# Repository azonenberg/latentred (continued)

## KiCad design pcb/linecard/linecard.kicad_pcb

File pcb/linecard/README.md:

# 24-port non-PoE 10/100/1000baseT QSGMII line card

Input: 12V at 1.25A max, fused at 3A to be conservative.

Expect ~15W max power consumption, less under typical operation

## ERRATA

v0.1: right LED on the RJ45 is swapped between upper and lower ports

## Power

### Needs

* VDD (1.0V): 1.15A per PHY, 2.3A total
* VDD_A (1.0V): 180 mA per PHY, 360 mA total
* VDD_AH (2.5V): 1.37A per PHY, 2.74A total
* VDD_AL (1.0V): 190 mA per PHY, 380 total
* VDD_IO (2.5V): 60 mA per PHY, 120 mA total
* VDD_VS (1.0V): 90 mA per PHY, 180 mA total
* Plus a 3.3V standby rail for the management MCU

## I2C address map

* 0x80: INA230 on 3V3
* 0x82: INA230 on 2V5
* 0x84: INA230 on 1V0
* 0x86: INA230 on 1V0_2
* 0x90: AT30TS74 near PHY 0
* 0x92: AT30ST74 near PHY 1
* 0x94: AT30TS74 near power supply

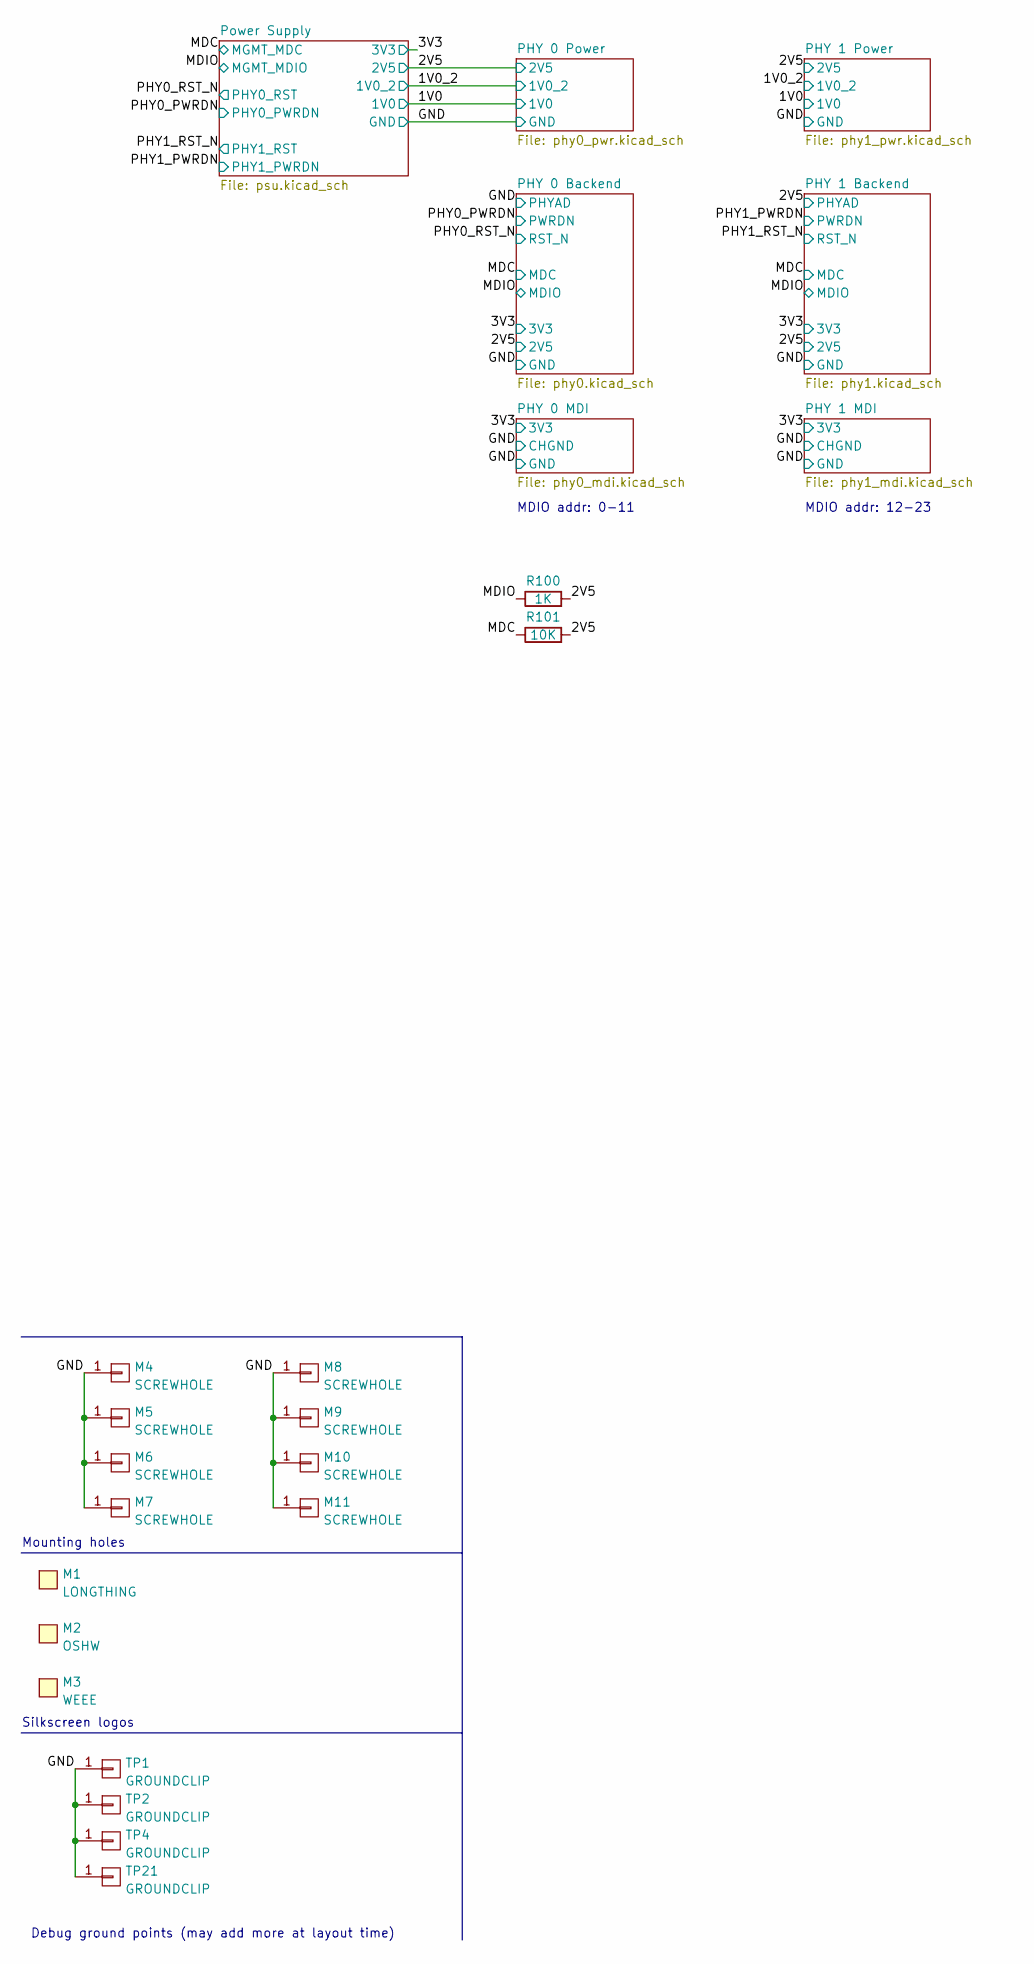
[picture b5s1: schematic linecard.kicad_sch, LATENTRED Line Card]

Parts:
M1: LONGTHING; LONGTHING-600DPI
M2: OSHW; Logo_silk_OSHW_6x6mm
M3: WEEE; Logo_silk_WEEE_3.4x5mm
M4, M5, M6, M7, M8, M9, M10, M11: SCREWHOLE; MECHANICAL_CLEARANCEHOLE_4_40
R100: 1K; EIA_0402_RES_NOSILK
R101: 10K; EIA_0402_RES_NOSILK
TP1, TP2, TP4, TP21: GROUNDCLIP; TESTPOINT_SMT_KEYSTONE_5016

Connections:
/2V5: R100.2, R101.2; also elsewhere on the board
/MDC: R101.1; also elsewhere on the board
/MDIO: R100.1; also elsewhere on the board

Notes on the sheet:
Silkscreen logos
Debug ground points (may add more at layout time)
MDIO addr: 0-11
Mounting holes
MDIO addr: 12-23

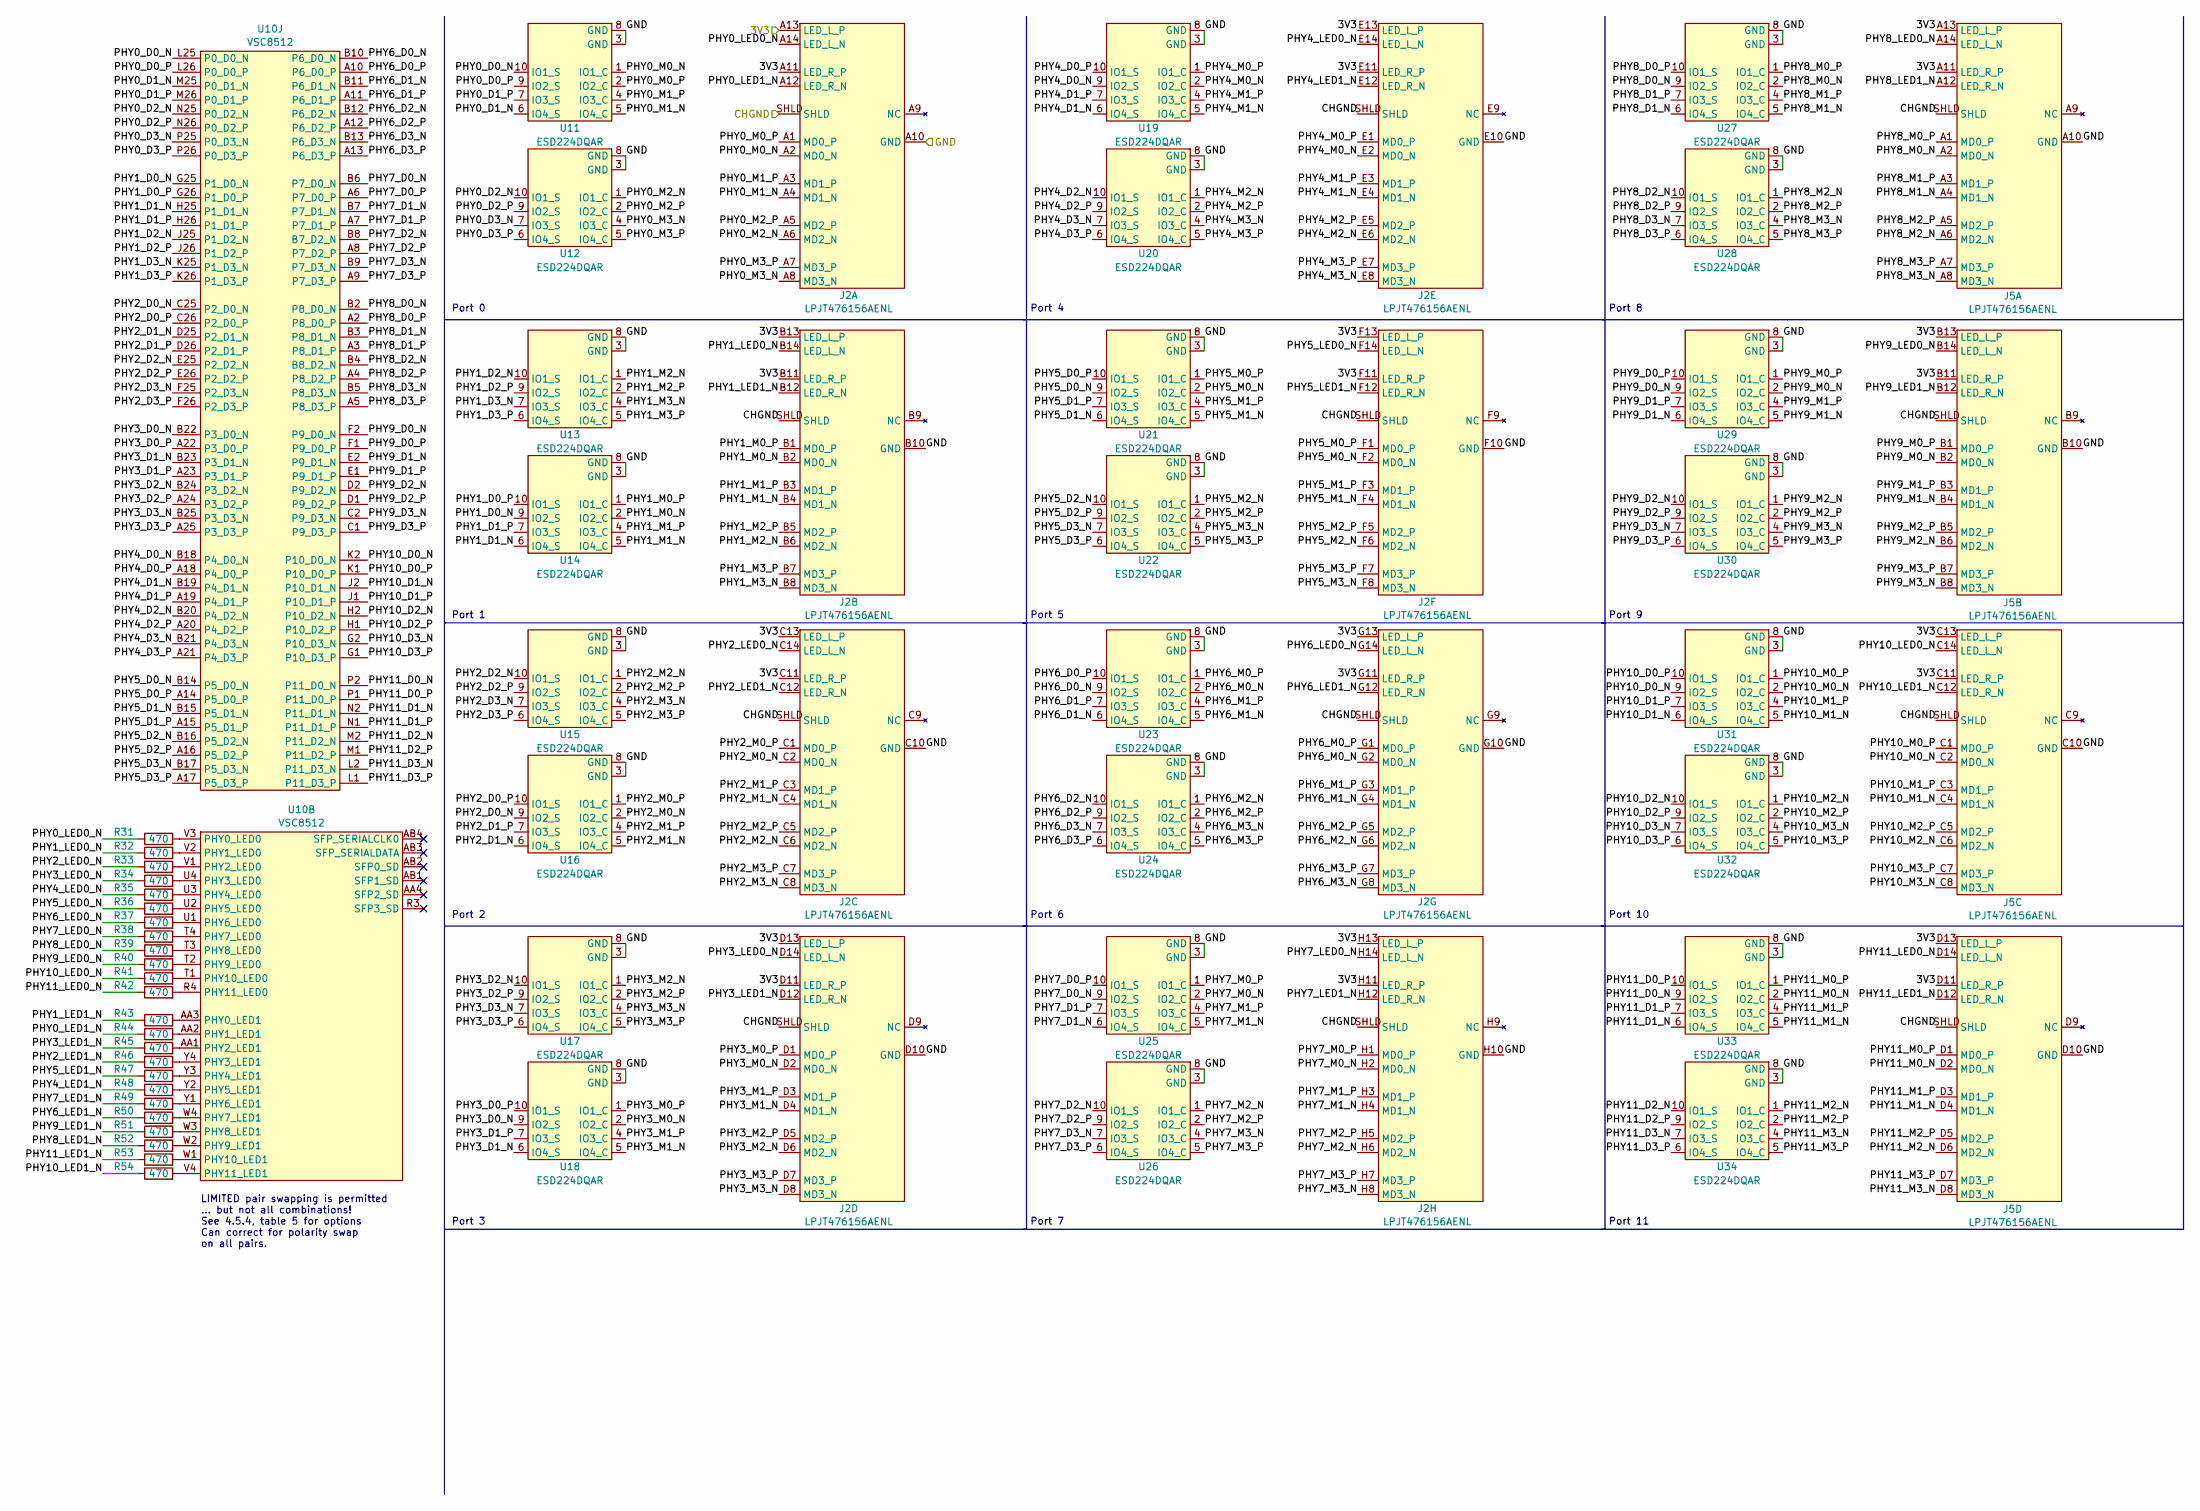
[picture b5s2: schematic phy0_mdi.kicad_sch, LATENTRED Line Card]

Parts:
J2, J5: LPJT476156AENL; CONN_LINKPP_LPJT476156AENL
R31, R32, R33, R34, R35, R36, R37, R38, R39, R40, R41, R42, R43, R44, R45, R46, R47, R48, R49, R50, R51, R52, R53, R54: 470; EIA_0402_RES_NOSILK
U10: VSC8512; BGA_676_27x27_FULLARRAY_1MM_FFG676
U11, U12, U13, U14, U15, U16, U17, U18, U19, U20, U21, U22, U23, U24, U25, U26, U27, U28, U29, U30, U31, U32, U33, U34: ESD224DQAR; DFN_10_0.5MM_2.5x1MM_TI_DQA

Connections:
/3V3: J2.A11 (LED_R_P), J2.A13 (LED_L_P), J2.B11 (LED_R_P), J2.B13 (LED_L_P), J2.C11 (LED_R_P), J2.C13 (LED_L_P), J2.D11 (LED_R_P), J2.D13 (LED_L_P), J2.E11 (LED_R_P), J2.E13 (LED_L_P), J2.F11 (LED_R_P), J2.F13 (LED_L_P), J2.G11 (LED_R_P), J2.G13 (LED_L_P), J2.H11 (LED_R_P), J2.H13 (LED_L_P), J5.A11 (LED_R_P), J5.A13 (LED_L_P), J5.B11 (LED_R_P), J5.B13 (LED_L_P), J5.C11 (LED_R_P), J5.C13 (LED_L_P), J5.D11 (LED_R_P), J5.D13 (LED_L_P); also elsewhere on the board
/PHY 0 MDI/PHY0_D0_N: U10.L25 (P0_D0_N), U11.10 (IO1_S)
/PHY 0 MDI/PHY0_D0_P: U10.L26 (P0_D0_P), U11.9 (IO2_S)
/PHY 0 MDI/PHY0_D1_N: U10.M25 (P0_D1_N), U11.6 (IO4_S)
/PHY 0 MDI/PHY0_D1_P: U10.M26 (P0_D1_P), U11.7 (IO3_S)
/PHY 0 MDI/PHY0_D2_N: U10.N25 (P0_D2_N), U12.10 (IO1_S)
/PHY 0 MDI/PHY0_D2_P: U10.N26 (P0_D2_P), U12.9 (IO2_S)
/PHY 0 MDI/PHY0_D3_N: U10.P25 (P0_D3_N), U12.7 (IO3_S)
/PHY 0 MDI/PHY0_D3_P: U10.P26 (P0_D3_P), U12.6 (IO4_S)
/PHY 0 MDI/PHY0_LED0_N: J2.A14 (LED_L_N), R31.1
/PHY 0 MDI/PHY0_LED1_N: J2.A12 (LED_R_N), R44.1
/PHY 0 MDI/PHY0_M0_N: J2.A2 (MD0_N), U11.1 (IO1_C)
/PHY 0 MDI/PHY0_M0_P: J2.A1 (MD0_P), U11.2 (IO2_C)
/PHY 0 MDI/PHY0_M1_N: J2.A4 (MD1_N), U11.5 (IO4_C)
/PHY 0 MDI/PHY0_M1_P: J2.A3 (MD1_P), U11.4 (IO3_C)
/PHY 0 MDI/PHY0_M2_N: J2.A6 (MD2_N), U12.1 (IO1_C)
/PHY 0 MDI/PHY0_M2_P: J2.A5 (MD2_P), U12.2 (IO2_C)
/PHY 0 MDI/PHY0_M3_N: J2.A8 (MD3_N), U12.4 (IO3_C)
/PHY 0 MDI/PHY0_M3_P: J2.A7 (MD3_P), U12.5 (IO4_C)
/PHY 0 MDI/PHY1_D0_N: U10.G25 (P1_D0_N), U14.9 (IO2_S)
/PHY 0 MDI/PHY1_D0_P: U10.G26 (P1_D0_P), U14.10 (IO1_S)
/PHY 0 MDI/PHY1_D1_N: U10.H25 (P1_D1_N), U14.6 (IO4_S)
/PHY 0 MDI/PHY1_D1_P: U10.H26 (P1_D1_P), U14.7 (IO3_S)
/PHY 0 MDI/PHY1_D2_N: U10.J25 (P1_D2_N), U13.10 (IO1_S)
/PHY 0 MDI/PHY1_D2_P: U10.J26 (P1_D2_P), U13.9 (IO2_S)
/PHY 0 MDI/PHY1_D3_N: U10.K25 (P1_D3_N), U13.7 (IO3_S)
/PHY 0 MDI/PHY1_D3_P: U10.K26 (P1_D3_P), U13.6 (IO4_S)
/PHY 0 MDI/PHY1_LED0_N: J2.B14 (LED_L_N), R32.1
/PHY 0 MDI/PHY1_LED1_N: J2.B12 (LED_R_N), R43.1
/PHY 0 MDI/PHY1_M0_N: J2.B2 (MD0_N), U14.2 (IO2_C)
/PHY 0 MDI/PHY1_M0_P: J2.B1 (MD0_P), U14.1 (IO1_C)
/PHY 0 MDI/PHY1_M1_N: J2.B4 (MD1_N), U14.5 (IO4_C)
/PHY 0 MDI/PHY1_M1_P: J2.B3 (MD1_P), U14.4 (IO3_C)
/PHY 0 MDI/PHY1_M2_N: J2.B6 (MD2_N), U13.1 (IO1_C)
/PHY 0 MDI/PHY1_M2_P: J2.B5 (MD2_P), U13.2 (IO2_C)
/PHY 0 MDI/PHY1_M3_N: J2.B8 (MD3_N), U13.4 (IO3_C)
/PHY 0 MDI/PHY1_M3_P: J2.B7 (MD3_P), U13.5 (IO4_C)
/PHY 0 MDI/PHY2_D0_N: U10.C25 (P2_D0_N), U16.9 (IO2_S)
/PHY 0 MDI/PHY2_D0_P: U10.C26 (P2_D0_P), U16.10 (IO1_S)
/PHY 0 MDI/PHY2_D1_N: U10.D25 (P2_D1_N), U16.6 (IO4_S)
/PHY 0 MDI/PHY2_D1_P: U10.D26 (P2_D1_P), U16.7 (IO3_S)
/PHY 0 MDI/PHY2_D2_N: U10.E25 (P2_D2_N), U15.10 (IO1_S)
/PHY 0 MDI/PHY2_D2_P: U10.E26 (P2_D2_P), U15.9 (IO2_S)
/PHY 0 MDI/PHY2_D3_N: U10.F25 (P2_D3_N), U15.7 (IO3_S)
/PHY 0 MDI/PHY2_D3_P: U10.F26 (P2_D3_P), U15.6 (IO4_S)
/PHY 0 MDI/PHY2_LED0_N: J2.C14 (LED_L_N), R33.1
/PHY 0 MDI/PHY2_LED1_N: J2.C12 (LED_R_N), R46.1
/PHY 0 MDI/PHY2_M0_N: J2.C2 (MD0_N), U16.2 (IO2_C)
/PHY 0 MDI/PHY2_M0_P: J2.C1 (MD0_P), U16.1 (IO1_C)
/PHY 0 MDI/PHY2_M1_N: J2.C4 (MD1_N), U16.5 (IO4_C)
/PHY 0 MDI/PHY2_M1_P: J2.C3 (MD1_P), U16.4 (IO3_C)
/PHY 0 MDI/PHY2_M2_N: J2.C6 (MD2_N), U15.1 (IO1_C)
/PHY 0 MDI/PHY2_M2_P: J2.C5 (MD2_P), U15.2 (IO2_C)
/PHY 0 MDI/PHY2_M3_N: J2.C8 (MD3_N), U15.4 (IO3_C)
/PHY 0 MDI/PHY2_M3_P: J2.C7 (MD3_P), U15.5 (IO4_C)
/PHY 0 MDI/PHY3_D0_N: U10.B22 (P3_D0_N), U18.9 (IO2_S)
/PHY 0 MDI/PHY3_D0_P: U10.A22 (P3_D0_P), U18.10 (IO1_S)
/PHY 0 MDI/PHY3_D1_N: U10.B23 (P3_D1_N), U18.6 (IO4_S)
/PHY 0 MDI/PHY3_D1_P: U10.A23 (P3_D1_P), U18.7 (IO3_S)
/PHY 0 MDI/PHY3_D2_N: U10.B24 (P3_D2_N), U17.10 (IO1_S)
/PHY 0 MDI/PHY3_D2_P: U10.A24 (P3_D2_P), U17.9 (IO2_S)
/PHY 0 MDI/PHY3_D3_N: U10.B25 (P3_D3_N), U17.7 (IO3_S)
/PHY 0 MDI/PHY3_D3_P: U10.A25 (P3_D3_P), U17.6 (IO4_S)
/PHY 0 MDI/PHY3_LED0_N: J2.D14 (LED_L_N), R34.1
/PHY 0 MDI/PHY3_LED1_N: J2.D12 (LED_R_N), R45.1
/PHY 0 MDI/PHY3_M0_N: J2.D2 (MD0_N), U18.2 (IO2_C)
/PHY 0 MDI/PHY3_M0_P: J2.D1 (MD0_P), U18.1 (IO1_C)
/PHY 0 MDI/PHY3_M1_N: J2.D4 (MD1_N), U18.5 (IO4_C)
/PHY 0 MDI/PHY3_M1_P: J2.D3 (MD1_P), U18.4 (IO3_C)
/PHY 0 MDI/PHY3_M2_N: J2.D6 (MD2_N), U17.1 (IO1_C)
/PHY 0 MDI/PHY3_M2_P: J2.D5 (MD2_P), U17.2 (IO2_C)
/PHY 0 MDI/PHY3_M3_N: J2.D8 (MD3_N), U17.4 (IO3_C)
/PHY 0 MDI/PHY3_M3_P: J2.D7 (MD3_P), U17.5 (IO4_C)
/PHY 0 MDI/PHY4_D0_N: U10.B18 (P4_D0_N), U19.9 (IO2_S)
/PHY 0 MDI/PHY4_D0_P: U10.A18 (P4_D0_P), U19.10 (IO1_S)
/PHY 0 MDI/PHY4_D1_N: U10.B19 (P4_D1_N), U19.6 (IO4_S)
/PHY 0 MDI/PHY4_D1_P: U10.A19 (P4_D1_P), U19.7 (IO3_S)
/PHY 0 MDI/PHY4_D2_N: U10.B20 (P4_D2_N), U20.10 (IO1_S)
/PHY 0 MDI/PHY4_D2_P: U10.A20 (P4_D2_P), U20.9 (IO2_S)
/PHY 0 MDI/PHY4_D3_N: U10.B21 (P4_D3_N), U20.7 (IO3_S)
/PHY 0 MDI/PHY4_D3_P: U10.A21 (P4_D3_P), U20.6 (IO4_S)
/PHY 0 MDI/PHY4_LED0_N: J2.E14 (LED_L_N), R35.1
/PHY 0 MDI/PHY4_LED1_N: J2.E12 (LED_R_N), R48.1
/PHY 0 MDI/PHY4_M0_N: J2.E2 (MD0_N), U19.2 (IO2_C)
/PHY 0 MDI/PHY4_M0_P: J2.E1 (MD0_P), U19.1 (IO1_C)
/PHY 0 MDI/PHY4_M1_N: J2.E4 (MD1_N), U19.5 (IO4_C)
/PHY 0 MDI/PHY4_M1_P: J2.E3 (MD1_P), U19.4 (IO3_C)
/PHY 0 MDI/PHY4_M2_N: J2.E6 (MD2_N), U20.1 (IO1_C)
/PHY 0 MDI/PHY4_M2_P: J2.E5 (MD2_P), U20.2 (IO2_C)
/PHY 0 MDI/PHY4_M3_N: J2.E8 (MD3_N), U20.4 (IO3_C)
/PHY 0 MDI/PHY4_M3_P: J2.E7 (MD3_P), U20.5 (IO4_C)
/PHY 0 MDI/PHY5_D0_N: U10.B14 (P5_D0_N), U21.9 (IO2_S)
/PHY 0 MDI/PHY5_D0_P: U10.A14 (P5_D0_P), U21.10 (IO1_S)
/PHY 0 MDI/PHY5_D1_N: U10.B15 (P5_D1_N), U21.6 (IO4_S)
/PHY 0 MDI/PHY5_D1_P: U10.A15 (P5_D1_P), U21.7 (IO3_S)
/PHY 0 MDI/PHY5_D2_N: U10.B16 (P5_D2_N), U22.10 (IO1_S)
/PHY 0 MDI/PHY5_D2_P: U10.A16 (P5_D2_P), U22.9 (IO2_S)
/PHY 0 MDI/PHY5_D3_N: U10.B17 (P5_D3_N), U22.7 (IO3_S)
/PHY 0 MDI/PHY5_D3_P: U10.A17 (P5_D3_P), U22.6 (IO4_S)
/PHY 0 MDI/PHY5_LED0_N: J2.F14 (LED_L_N), R36.1
/PHY 0 MDI/PHY5_LED1_N: J2.F12 (LED_R_N), R47.1
/PHY 0 MDI/PHY5_M0_N: J2.F2 (MD0_N), U21.2 (IO2_C)
/PHY 0 MDI/PHY5_M0_P: J2.F1 (MD0_P), U21.1 (IO1_C)
/PHY 0 MDI/PHY5_M1_N: J2.F4 (MD1_N), U21.5 (IO4_C)
/PHY 0 MDI/PHY5_M1_P: J2.F3 (MD1_P), U21.4 (IO3_C)
/PHY 0 MDI/PHY5_M2_N: J2.F6 (MD2_N), U22.1 (IO1_C)
/PHY 0 MDI/PHY5_M2_P: J2.F5 (MD2_P), U22.2 (IO2_C)
/PHY 0 MDI/PHY5_M3_N: J2.F8 (MD3_N), U22.4 (IO3_C)
/PHY 0 MDI/PHY5_M3_P: J2.F7 (MD3_P), U22.5 (IO4_C)
/PHY 0 MDI/PHY6_D0_N: U10.B10 (P6_D0_N), U23.9 (IO2_S)
/PHY 0 MDI/PHY6_D0_P: U10.A10 (P6_D0_P), U23.10 (IO1_S)
/PHY 0 MDI/PHY6_D1_N: U10.B11 (P6_D1_N), U23.6 (IO4_S)
/PHY 0 MDI/PHY6_D1_P: U10.A11 (P6_D1_P), U23.7 (IO3_S)
/PHY 0 MDI/PHY6_D2_N: U10.B12 (P6_D2_N), U24.10 (IO1_S)
/PHY 0 MDI/PHY6_D2_P: U10.A12 (P6_D2_P), U24.9 (IO2_S)
/PHY 0 MDI/PHY6_D3_N: U10.B13 (P6_D3_N), U24.7 (IO3_S)
/PHY 0 MDI/PHY6_D3_P: U10.A13 (P6_D3_P), U24.6 (IO4_S)
/PHY 0 MDI/PHY6_LED0_N: J2.G14 (LED_L_N), R37.1
/PHY 0 MDI/PHY6_LED1_N: J2.G12 (LED_R_N), R50.1
/PHY 0 MDI/PHY6_M0_N: J2.G2 (MD0_N), U23.2 (IO2_C)
/PHY 0 MDI/PHY6_M0_P: J2.G1 (MD0_P), U23.1 (IO1_C)
/PHY 0 MDI/PHY6_M1_N: J2.G4 (MD1_N), U23.5 (IO4_C)
/PHY 0 MDI/PHY6_M1_P: J2.G3 (MD1_P), U23.4 (IO3_C)
/PHY 0 MDI/PHY6_M2_N: J2.G6 (MD2_N), U24.1 (IO1_C)
/PHY 0 MDI/PHY6_M2_P: J2.G5 (MD2_P), U24.2 (IO2_C)
/PHY 0 MDI/PHY6_M3_N: J2.G8 (MD3_N), U24.4 (IO3_C)
/PHY 0 MDI/PHY6_M3_P: J2.G7 (MD3_P), U24.5 (IO4_C)
/PHY 0 MDI/PHY7_D0_N: U10.B6 (P7_D0_N), U25.9 (IO2_S)
/PHY 0 MDI/PHY7_D0_P: U10.A6 (P7_D0_P), U25.10 (IO1_S)
/PHY 0 MDI/PHY7_D1_N: U10.B7 (P7_D1_N), U25.6 (IO4_S)
/PHY 0 MDI/PHY7_D1_P: U10.A7 (P7_D1_P), U25.7 (IO3_S)
/PHY 0 MDI/PHY7_D2_N: U10.B8 (B7_D2_N), U26.10 (IO1_S)
/PHY 0 MDI/PHY7_D2_P: U10.A8 (P7_D2_P), U26.9 (IO2_S)
/PHY 0 MDI/PHY7_D3_N: U10.B9 (P7_D3_N), U26.7 (IO3_S)
/PHY 0 MDI/PHY7_D3_P: U10.A9 (P7_D3_P), U26.6 (IO4_S)
/PHY 0 MDI/PHY7_LED0_N: J2.H14 (LED_L_N), R38.1
/PHY 0 MDI/PHY7_LED1_N: J2.H12 (LED_R_N), R49.1
/PHY 0 MDI/PHY7_M0_N: J2.H2 (MD0_N), U25.2 (IO2_C)
/PHY 0 MDI/PHY7_M0_P: J2.H1 (MD0_P), U25.1 (IO1_C)
/PHY 0 MDI/PHY7_M1_N: J2.H4 (MD1_N), U25.5 (IO4_C)
/PHY 0 MDI/PHY7_M1_P: J2.H3 (MD1_P), U25.4 (IO3_C)
/PHY 0 MDI/PHY7_M2_N: J2.H6 (MD2_N), U26.1 (IO1_C)
/PHY 0 MDI/PHY7_M2_P: J2.H5 (MD2_P), U26.2 (IO2_C)
/PHY 0 MDI/PHY7_M3_N: J2.H8 (MD3_N), U26.4 (IO3_C)
/PHY 0 MDI/PHY7_M3_P: J2.H7 (MD3_P), U26.5 (IO4_C)
/PHY 0 MDI/PHY8_D0_N: U10.B2 (P8_D0_N), U27.9 (IO2_S)
/PHY 0 MDI/PHY8_D0_P: U10.A2 (P8_D0_P), U27.10 (IO1_S)
/PHY 0 MDI/PHY8_D1_N: U10.B3 (P8_D1_N), U27.6 (IO4_S)
/PHY 0 MDI/PHY8_D1_P: U10.A3 (P8_D1_P), U27.7 (IO3_S)
/PHY 0 MDI/PHY8_D2_N: U10.B4 (B8_D2_N), U28.10 (IO1_S)
/PHY 0 MDI/PHY8_D2_P: U10.A4 (P8_D2_P), U28.9 (IO2_S)
/PHY 0 MDI/PHY8_D3_N: U10.B5 (P8_D3_N), U28.7 (IO3_S)
/PHY 0 MDI/PHY8_D3_P: U10.A5 (P8_D3_P), U28.6 (IO4_S)
/PHY 0 MDI/PHY8_LED0_N: J5.A14 (LED_L_N), R39.1
/PHY 0 MDI/PHY8_LED1_N: J5.A12 (LED_R_N), R52.1
/PHY 0 MDI/PHY8_M0_N: J5.A2 (MD0_N), U27.2 (IO2_C)
/PHY 0 MDI/PHY8_M0_P: J5.A1 (MD0_P), U27.1 (IO1_C)
/PHY 0 MDI/PHY8_M1_N: J5.A4 (MD1_N), U27.5 (IO4_C)
/PHY 0 MDI/PHY8_M1_P: J5.A3 (MD1_P), U27.4 (IO3_C)
/PHY 0 MDI/PHY8_M2_N: J5.A6 (MD2_N), U28.1 (IO1_C)
/PHY 0 MDI/PHY8_M2_P: J5.A5 (MD2_P), U28.2 (IO2_C)
/PHY 0 MDI/PHY8_M3_N: J5.A8 (MD3_N), U28.4 (IO3_C)
/PHY 0 MDI/PHY8_M3_P: J5.A7 (MD3_P), U28.5 (IO4_C)
/PHY 0 MDI/PHY9_D0_N: U10.F2 (P9_D0_N), U29.9 (IO2_S)
/PHY 0 MDI/PHY9_D0_P: U10.F1 (P9_D0_P), U29.10 (IO1_S)
/PHY 0 MDI/PHY9_D1_N: U10.E2 (P9_D1_N), U29.6 (IO4_S)
/PHY 0 MDI/PHY9_D1_P: U10.E1 (P9_D1_P), U29.7 (IO3_S)
/PHY 0 MDI/PHY9_D2_N: U10.D2 (P9_D2_N), U30.10 (IO1_S)
/PHY 0 MDI/PHY9_D2_P: U10.D1 (P9_D2_P), U30.9 (IO2_S)
/PHY 0 MDI/PHY9_D3_N: U10.C2 (P9_D3_N), U30.7 (IO3_S)
/PHY 0 MDI/PHY9_D3_P: U10.C1 (P9_D3_P), U30.6 (IO4_S)
/PHY 0 MDI/PHY9_LED0_N: J5.B14 (LED_L_N), R40.1
/PHY 0 MDI/PHY9_LED1_N: J5.B12 (LED_R_N), R51.1
/PHY 0 MDI/PHY9_M0_N: J5.B2 (MD0_N), U29.2 (IO2_C)
/PHY 0 MDI/PHY9_M0_P: J5.B1 (MD0_P), U29.1 (IO1_C)
/PHY 0 MDI/PHY9_M1_N: J5.B4 (MD1_N), U29.5 (IO4_C)
/PHY 0 MDI/PHY9_M1_P: J5.B3 (MD1_P), U29.4 (IO3_C)
/PHY 0 MDI/PHY9_M2_N: J5.B6 (MD2_N), U30.1 (IO1_C)
/PHY 0 MDI/PHY9_M2_P: J5.B5 (MD2_P), U30.2 (IO2_C)
/PHY 0 MDI/PHY9_M3_N: J5.B8 (MD3_N), U30.4 (IO3_C)
/PHY 0 MDI/PHY9_M3_P: J5.B7 (MD3_P), U30.5 (IO4_C)
/PHY 0 MDI/PHY10_D0_N: U10.K2 (P10_D0_N), U31.9 (IO2_S)
/PHY 0 MDI/PHY10_D0_P: U10.K1 (P10_D0_P), U31.10 (IO1_S)
/PHY 0 MDI/PHY10_D1_N: U10.J2 (P10_D1_N), U31.6 (IO4_S)
/PHY 0 MDI/PHY10_D1_P: U10.J1 (P10_D1_P), U31.7 (IO3_S)
/PHY 0 MDI/PHY10_D2_N: U10.H2 (P10_D2_N), U32.10 (IO1_S)
/PHY 0 MDI/PHY10_D2_P: U10.H1 (P10_D2_P), U32.9 (IO2_S)
/PHY 0 MDI/PHY10_D3_N: U10.G2 (P10_D3_N), U32.7 (IO3_S)
/PHY 0 MDI/PHY10_D3_P: U10.G1 (P10_D3_P), U32.6 (IO4_S)
/PHY 0 MDI/PHY10_LED0_N: J5.C14 (LED_L_N), R41.1
/PHY 0 MDI/PHY10_LED1_N: J5.C12 (LED_R_N), R54.1
/PHY 0 MDI/PHY10_M0_N: J5.C2 (MD0_N), U31.2 (IO2_C)
/PHY 0 MDI/PHY10_M0_P: J5.C1 (MD0_P), U31.1 (IO1_C)
/PHY 0 MDI/PHY10_M1_N: J5.C4 (MD1_N), U31.5 (IO4_C)
/PHY 0 MDI/PHY10_M1_P: J5.C3 (MD1_P), U31.4 (IO3_C)
/PHY 0 MDI/PHY10_M2_N: J5.C6 (MD2_N), U32.1 (IO1_C)
/PHY 0 MDI/PHY10_M2_P: J5.C5 (MD2_P), U32.2 (IO2_C)
/PHY 0 MDI/PHY10_M3_N: J5.C8 (MD3_N), U32.4 (IO3_C)
/PHY 0 MDI/PHY10_M3_P: J5.C7 (MD3_P), U32.5 (IO4_C)
/PHY 0 MDI/PHY11_D0_N: U10.P2 (P11_D0_N), U33.9 (IO2_S)
/PHY 0 MDI/PHY11_D0_P: U10.P1 (P11_D0_P), U33.10 (IO1_S)
/PHY 0 MDI/PHY11_D1_N: U10.N2 (P11_D1_N), U33.6 (IO4_S)
/PHY 0 MDI/PHY11_D1_P: U10.N1 (P11_D1_P), U33.7 (IO3_S)
/PHY 0 MDI/PHY11_D2_N: U10.M2 (P11_D2_N), U34.10 (IO1_S)
/PHY 0 MDI/PHY11_D2_P: U10.M1 (P11_D2_P), U34.9 (IO2_S)
/PHY 0 MDI/PHY11_D3_N: U10.L2 (P11_D3_N), U34.7 (IO3_S)
/PHY 0 MDI/PHY11_D3_P: U10.L1 (P11_D3_P), U34.6 (IO4_S)
/PHY 0 MDI/PHY11_LED0_N: J5.D14 (LED_L_N), R42.1
/PHY 0 MDI/PHY11_LED1_N: J5.D12 (LED_R_N), R53.1
/PHY 0 MDI/PHY11_M0_N: J5.D2 (MD0_N), U33.2 (IO2_C)
/PHY 0 MDI/PHY11_M0_P: J5.D1 (MD0_P), U33.1 (IO1_C)
/PHY 0 MDI/PHY11_M1_N: J5.D4 (MD1_N), U33.5 (IO4_C)
/PHY 0 MDI/PHY11_M1_P: J5.D3 (MD1_P), U33.4 (IO3_C)
/PHY 0 MDI/PHY11_M2_N: J5.D6 (MD2_N), U34.1 (IO1_C)
/PHY 0 MDI/PHY11_M2_P: J5.D5 (MD2_P), U34.2 (IO2_C)
/PHY 0 MDI/PHY11_M3_N: J5.D8 (MD3_N), U34.4 (IO3_C)
/PHY 0 MDI/PHY11_M3_P: J5.D7 (MD3_P), U34.5 (IO4_C)
unnamed: R31.2, U10.V3 (PHY0_LED0)
unnamed: R43.2, U10.AA3 (PHY0_LED1)
unnamed: R32.2, U10.V2 (PHY1_LED0)
unnamed: R44.2, U10.AA2 (PHY1_LED1)
unnamed: R33.2, U10.V1 (PHY2_LED0)
unnamed: R45.2, U10.AA1 (PHY2_LED1)
unnamed: R34.2, U10.U4 (PHY3_LED0)
unnamed: R46.2, U10.Y4 (PHY3_LED1)
unnamed: R35.2, U10.U3 (PHY4_LED0)
unnamed: R47.2, U10.Y3 (PHY4_LED1)
unnamed: R36.2, U10.U2 (PHY5_LED0)
unnamed: R48.2, U10.Y2 (PHY5_LED1)
unnamed: R37.2, U10.U1 (PHY6_LED0)
unnamed: R49.2, U10.Y1 (PHY6_LED1)
unnamed: R38.2, U10.T4 (PHY7_LED0)
unnamed: R50.2, U10.W4 (PHY7_LED1)
unnamed: R39.2, U10.T3 (PHY8_LED0)
unnamed: R51.2, U10.W3 (PHY8_LED1)
unnamed: R40.2, U10.T2 (PHY9_LED0)
unnamed: R52.2, U10.W2 (PHY9_LED1)
unnamed: R41.2, U10.T1 (PHY10_LED0)
unnamed: R53.2, U10.W1 (PHY10_LED1)
unnamed: R42.2, U10.R4 (PHY11_LED0)
unnamed: R54.2, U10.V4 (PHY11_LED1)

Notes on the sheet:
Port 9
Port 2
Port 7
Port 1
Port 5
Port 11
LIMITED pair swapping is permitted ... but not all combinations! See 4.5.4, table 5 for options Can correct for polarity swap on all pairs.
Port 10
Port 3
Port 4
Port 0
Port 6
Port 8

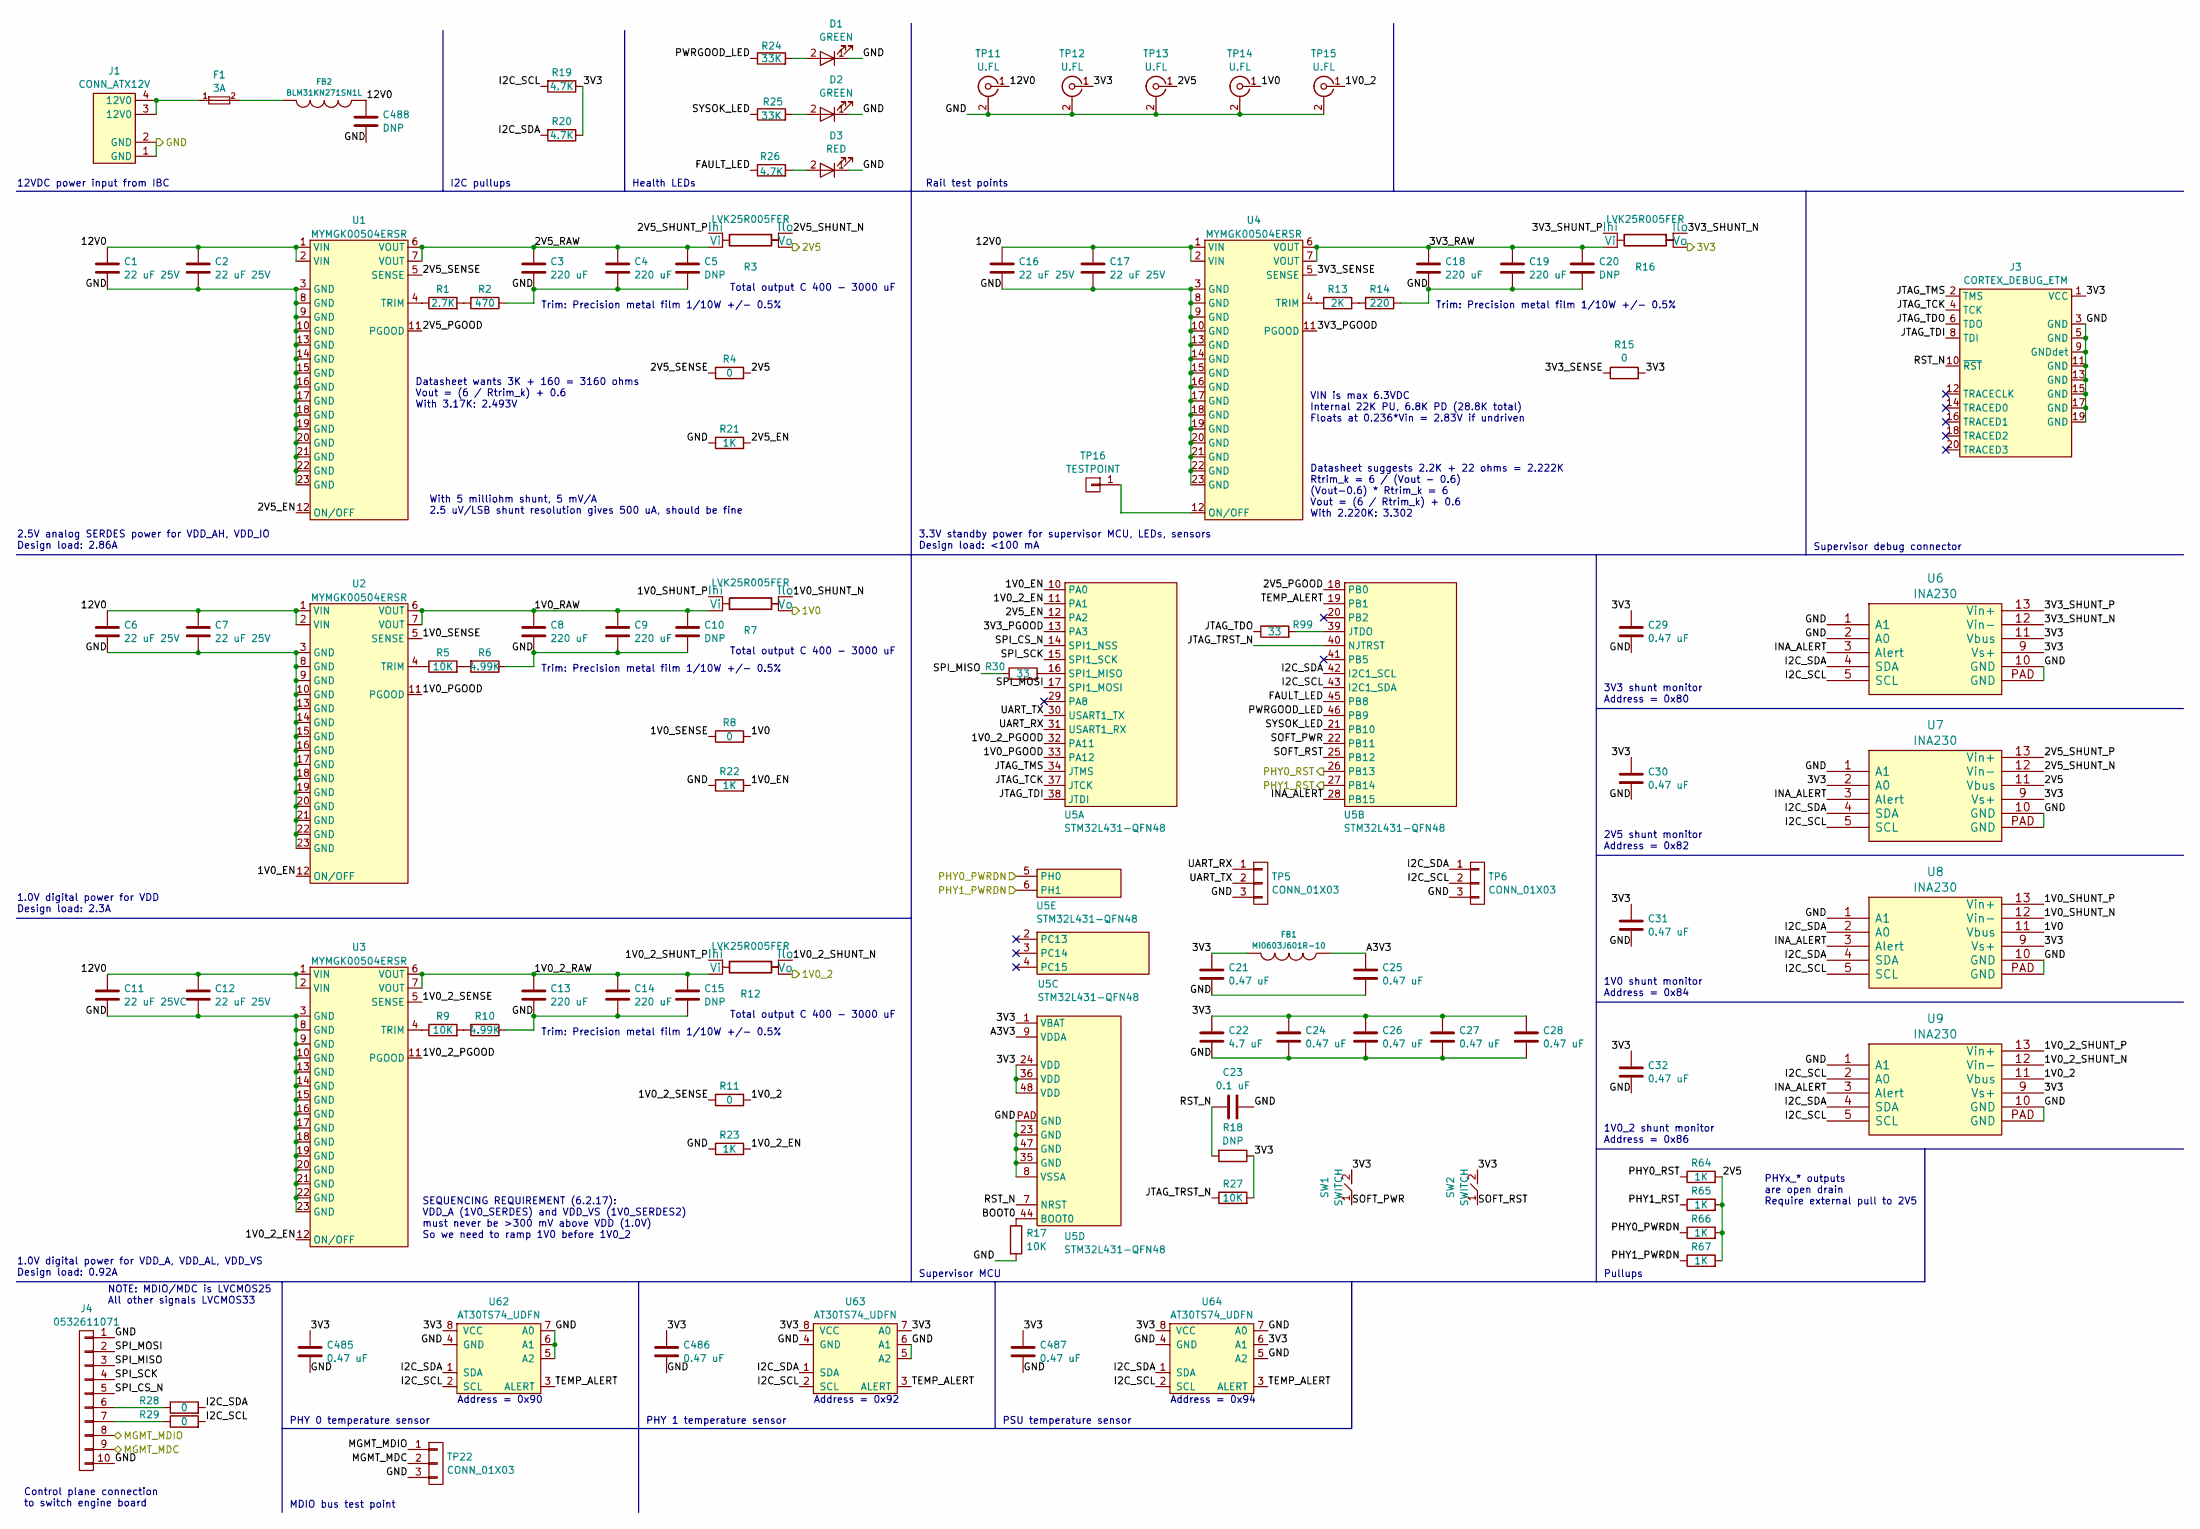
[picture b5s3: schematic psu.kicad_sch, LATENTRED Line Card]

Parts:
C1, C2, C6, C7, C12, C16, C17: 22 uF 25V; EIA_1812_CAP_NOSILK
C3, C4, C8, C9, C13, C14, C18, C19: 220 uF; EIA_1210_CAP_NOSILK
C5, C10, C15, C20: DNP; EIA_1210_CAP_NOSILK
C11: 22 uF 25VC; EIA_1812_CAP_NOSILK
C21, C24, C25, C26, C27, C28, C29, C30, C31, C32, C485, C486, C487: 0.47 uF; EIA_0402_CAP_NOSILK
C22: 4.7 uF; EIA_0603_CAP_NOSILK
C23: 0.1 uF; EIA_0402_CAP_NOSILK
C488: DNP; CAP_AL_10MM_SMT
D1, D2: GREEN; EIA_0402_LED
D3: RED; EIA_0402_LED
F1: 3A; EIA_0402_RES_NOSILK
FB1: MI0603J601R-10; EIA_0603_INDUCTOR_NOSILK
FB2: BLM31KN271SN1L; EIA_1206_CAP_NOSILK
J1: CONN_ATX12V; CONN_MOLEX_MINIFITJR_4POS_0039291048
J3: CORTEX_DEBUG_ETM; CONN_HEADER_1.27MM_2x10_SMT_SAMTEC_FTSH-110-01-L-DV-K
J4: 0532611071; CONN_MOLEX_PICOBLADE_10POS_0532611071
R1: 2.7K; EIA_0402_RES_NOSILK
R2: 470; EIA_0402_RES_NOSILK
R3, R7, R12, R16: LVK25R005FER; OHMITE_LVK25
R4, R8, R11, R15, R28, R29: 0; EIA_0402_RES_NOSILK
R5, R9, R17, R27: 10K; EIA_0402_RES_NOSILK
R6, R10: 4.99K; EIA_0402_RES_NOSILK
R13: 2K; EIA_0402_RES_NOSILK
R14: 220; EIA_0402_RES_NOSILK
R18: DNP; EIA_0402_RES_NOSILK
R19, R20, R26: 4.7K; EIA_0402_RES_NOSILK
R21, R22, R23, R64, R65, R66, R67: 1K; EIA_0402_RES_NOSILK
R24, R25: 33K; EIA_0402_RES_NOSILK
R30, R99: 33; EIA_0402_RES_NOSILK
SW1, SW2: SWITCH; SWITCH_RAFI_MICON_5
TP5, TP6, TP22: CONN_01X03; CONN_HEADER_2.54MM_1x3_REFLOW
TP11, TP12, TP13, TP14, TP15: U.FL; CONN_U.FL_TE_1909763-1
TP16: TESTPOINT; TESTPOINT_SMT_0.5MM
U1, U2, U3, U4: MYMGK00504ERSR; MODULE_MURATA_MYMGK00504ERSR
U5: STM32L431-QFN48; QFN_48_0.5MM_7x7MM
U6, U7, U8, U9: INA230; QFN_16_0.5MM_3x3MM
U62, U63, U64: AT30TS74_UDFN; DFN_8_0.5MM_2x3MM_TALL

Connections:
/1V0: R7.2 (Vo), R8.2, TP14.1 (In), U8.11 (Vbus); also elsewhere on the board
/1V0_2: R11.2, R12.2 (Vo), TP15.1 (In), U9.11 (Vbus); also elsewhere on the board
/2V5: R3.2 (Vo), R4.2, R64.2, R65.2, R66.2, R67.2, TP13.1 (In), U7.11 (Vbus); also elsewhere on the board
/3V3: C21.1, C22.1, C24.1, C26.1, C27.1, C28.1, C29.1, C30.1, C31.1, C32.1, C485.1, C486.1, C487.1, FB1.2, J3.1 (VCC), R15.2, R16.2 (Vo), R18.1, R19.1, R20.1, R27.2, SW1.2, SW2.2, TP12.1 (In), U5.1 (VBAT), U5.24 (VDD), U5.36 (VDD), U5.48 (VDD), U6.9 (Vs+), U6.11 (Vbus), U7.2 (A0), U7.9 (Vs+), U8.9 (Vs+), U9.9 (Vs+), U62.8 (VCC), U63.7 (A0), U63.8 (VCC), U64.6 (A1), U64.8 (VCC); also elsewhere on the board
/MDC: J4.9, TP22.2; also elsewhere on the board
/MDIO: J4.8, TP22.1; also elsewhere on the board
/PHY0_PWRDN: R66.1, U5.5 (PH0); also elsewhere on the board
/PHY0_RST_N: R64.1, U5.26 (PB13); also elsewhere on the board
/PHY1_PWRDN: R67.1, U5.6 (PH1); also elsewhere on the board
/PHY1_RST_N: R65.1, U5.27 (PB14); also elsewhere on the board
/Power Supply/1V0_2_EN: R23.2, U3.12 (ON/OFF), U5.11 (PA1)
/Power Supply/1V0_2_PGOOD: U3.11 (PGOOD), U5.32 (PA11)
/Power Supply/1V0_2_RAW: C13.1, C14.1, C15.1, R12.4 (Vi), U3.6 (VOUT), U3.7 (VOUT)
/Power Supply/1V0_2_SENSE: R11.1, U3.5 (SENSE)
/Power Supply/1V0_2_SHUNT_N: R12.1 (Ilo), U9.12 (Vin-)
/Power Supply/1V0_2_SHUNT_P: R12.3 (Ihi), U9.13 (Vin+)
/Power Supply/1V0_EN: R22.2, U2.12 (ON/OFF), U5.10 (PA0)
/Power Supply/1V0_PGOOD: U2.11 (PGOOD), U5.33 (PA12)
/Power Supply/1V0_RAW: C8.1, C9.1, C10.1, R7.4 (Vi), U2.6 (VOUT), U2.7 (VOUT)
/Power Supply/1V0_SENSE: R8.1, U2.5 (SENSE)
/Power Supply/1V0_SHUNT_N: R7.1 (Ilo), U8.12 (Vin-)
/Power Supply/1V0_SHUNT_P: R7.3 (Ihi), U8.13 (Vin+)
/Power Supply/2V5_EN: R21.2, U1.12 (ON/OFF), U5.12 (PA2)
/Power Supply/2V5_PGOOD: U1.11 (PGOOD), U5.18 (PB0)
/Power Supply/2V5_RAW: C3.1, C4.1, C5.1, R3.4 (Vi), U1.6 (VOUT), U1.7 (VOUT)
/Power Supply/2V5_SENSE: R4.1, U1.5 (SENSE)
/Power Supply/2V5_SHUNT_N: R3.1 (Ilo), U7.12 (Vin-)
/Power Supply/2V5_SHUNT_P: R3.3 (Ihi), U7.13 (Vin+)
/Power Supply/3V3_PGOOD: U4.11 (PGOOD), U5.13 (PA3)
/Power Supply/3V3_RAW: C18.1, C19.1, C20.1, R16.4 (Vi), U4.6 (VOUT), U4.7 (VOUT)
/Power Supply/3V3_SENSE: R15.1, U4.5 (SENSE)
/Power Supply/3V3_SHUNT_N: R16.1 (Ilo), U6.12 (Vin-)
/Power Supply/3V3_SHUNT_P: R16.3 (Ihi), U6.13 (Vin+)
/Power Supply/12V0: C1.1, C2.1, C6.1, C7.1, C11.1, C12.1, C16.1, C17.1, C488.1, FB2.1, TP11.1 (In), U1.1 (VIN), U1.2 (VIN), U2.1 (VIN), U2.2 (VIN), U3.1 (VIN), U3.2 (VIN), U4.1 (VIN), U4.2 (VIN)
/Power Supply/A3V3: C25.1, FB1.1, U5.9 (VDDA)
/Power Supply/BOOT0: R17.1, U5.44 (BOOT0)
/Power Supply/FAULT_LED: R26.1, U5.45 (PB8)
/Power Supply/I2C_SCL: R19.2, R29.2, TP6.2, U5.43 (I2C1_SDA), U6.5 (SCL), U7.5 (SCL), U8.5 (SCL), U9.2 (A0), U9.5 (SCL), U62.2 (SCL), U63.2 (SCL), U64.2 (SCL)
/Power Supply/I2C_SDA: R20.2, R28.2, TP6.1, U5.42 (I2C1_SCL), U6.4 (SDA), U7.4 (SDA), U8.2 (A0), U8.4 (SDA), U9.4 (SDA), U62.1 (SDA), U63.1 (SDA), U64.1 (SDA)
/Power Supply/INA_ALERT: U5.28 (PB15), U6.3 (Alert), U7.3 (Alert), U8.3 (Alert), U9.3 (Alert)
/Power Supply/JTAG_TCK: J3.4 (TCK), U5.37 (JTCK)
/Power Supply/JTAG_TDI: J3.8 (TDI), U5.38 (JTDI)
/Power Supply/JTAG_TDO: J3.6 (TDO), R99.1
/Power Supply/JTAG_TMS: J3.2 (TMS), U5.34 (JTMS)
/Power Supply/JTAG_TRST_N: R27.1, U5.40 (NJTRST)
/Power Supply/PWRGOOD_LED: R24.1, U5.46 (PB9)
/Power Supply/RST_N: C23.1, J3.10 (~RST), R18.2, U5.7 (NRST)
/Power Supply/SOFT_PWR: SW1.1, U5.22 (PB11)
/Power Supply/SOFT_RST: SW2.1, U5.25 (PB12)
/Power Supply/SPI_CS_N: J4.5, U5.14 (SPI1_NSS)
/Power Supply/SPI_MISO: J4.3, R30.1
/Power Supply/SPI_MOSI: J4.2, U5.17 (SPI1_MOSI)
/Power Supply/SPI_SCK: J4.4, U5.15 (SPI1_SCK)
/Power Supply/SYSOK_LED: R25.1, U5.21 (PB10)
/Power Supply/TEMP_ALERT: U5.19 (PB1), U62.3 (ALERT), U63.3 (ALERT), U64.3 (ALERT)
/Power Supply/UART_RX: TP5.1, U5.31 (USART1_RX)
/Power Supply/UART_TX: TP5.2, U5.30 (USART1_TX)
unnamed: D1.2 (A), R24.2
unnamed: D2.2 (A), R25.2
unnamed: D3.2 (A), R26.2
unnamed: F1.1, J1.3 (12V0), J1.4 (12V0)
unnamed: F1.2, FB2.2
unnamed: J4.6, R28.1
unnamed: J4.7, R29.1
unnamed: R1.2, R2.2
unnamed: R5.2, R6.2
unnamed: R9.2, R10.2
unnamed: R13.2, R14.2
unnamed: TP16.1, U4.12 (ON/OFF)
unnamed: R1.1, U1.4 (TRIM)
unnamed: R5.1, U2.4 (TRIM)
unnamed: R9.1, U3.4 (TRIM)
unnamed: R13.1, U4.4 (TRIM)
unnamed: R30.2, U5.16 (SPI1_MISO)
unnamed: R99.2, U5.39 (JTDO)

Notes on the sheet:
SEQUENCING REQUIREMENT (6.2.17): VDD_A (1V0_SERDES) and VDD_VS (1V0_SERDES2) must never be >300 mV above VDD (1.0V) So we need to ramp 1V0 before 1V0_2
Health LEDs
VIN is max 6.3VDC Internal 22K PU, 6.8K PD (28.8K total) Floats at 0.236*Vin = 2.83V if undriven
3.3V standby power for supervisor MCU, LEDs, sensors Design load: <100 mA
12VDC power input from IBC
Address = 0x92
Trim: Precision metal film 1/10W +/- 0.5%
Control plane connection to switch engine board
PSU temperature sensor
Pullups
PHY 1 temperature sensor
I2C pullups
2V5 shunt monitor Address = 0x82
Address = 0x94
2.5V analog SERDES power for VDD_AH, VDD_IO Design load: 2.86A
1.0V digital power for VDD_A, VDD_AL, VDD_VS Design load: 0.92A
1.0V digital power for VDD Design load: 2.3A
Total output C 400 - 3000 uF
Datasheet wants 3K + 160 = 3160 ohms Vout = (6 / Rtrim_k) + 0.6 With 3.17K: 2.493V
PHY 0 temperature sensor
Supervisor MCU
NOTE: MDIO/MDC is LVCMOS25 All other signals LVCMOS33
3V3 shunt monitor Address = 0x80
MDIO bus test point
1V0 shunt monitor Address = 0x84
Supervisor debug connector
PHYx_* outputs are open drain Require external pull to 2V5
With 5 milliohm shunt, 5 mV/A 2.5 uV/LSB shunt resolution gives 500 uA, should be fine
Rail test points
1V0_2 shunt monitor Address = 0x86
Datasheet suggests 2.2K + 22 ohms = 2.222K Rtrim_k = 6 / (Vout - 0.6) (Vout-0.6) * Rtrim_k = 6 Vout = (6 / Rtrim_k) + 0.6 With 2.220K: 3.302
Address = 0x90
